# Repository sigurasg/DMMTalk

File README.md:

# DMMTalk

A battery-powered appendix to UNI-T 61E that speaks the settings and readings.

# TODO

* Add photodiode and amplifier for serial reception.
* Add button.
* Add volume control.
  * These two might take the form of a quadrature encoder with a button.
* Add headphone jack.
* Find a suitable SPI FLASH ROM.
  * Maybe [AT45DB081E
](http://www.adestotech.com/wp-content/uploads/DS-45DB081E_028.pdf)
  * Create a library component for same.
* Wire MSP430G2553 up.
  * RST/TEST go to RTS/CTS through resistors to allow BSL.
  * Need to find out how FT230 behaves without power, hopefully its outputs are
    3-state.
  * Even if it's tri-state, it'll conduct through the ESD protection diode, so
    this requires a switch to isolate the powered-down serial chip from
    the reset pin, as well as the TEST pin, to make sure in-circuit programming
    through the two-wire protocol works. Maybe something like
    http://www.onsemi.com/pub_link/Collateral/NL7WB66-D.PDF.
  * UCA0 or UCB0 drives the SPI bus.
  * One pin controls the analog power switch.
* Find suitable rail-to-rail op-amps.
  * Need 1.8V operating voltage at the bottom.
  * Need reasonable output current drive capability.
  * Maybe a bridge-drive headphone or speaker amp is better?

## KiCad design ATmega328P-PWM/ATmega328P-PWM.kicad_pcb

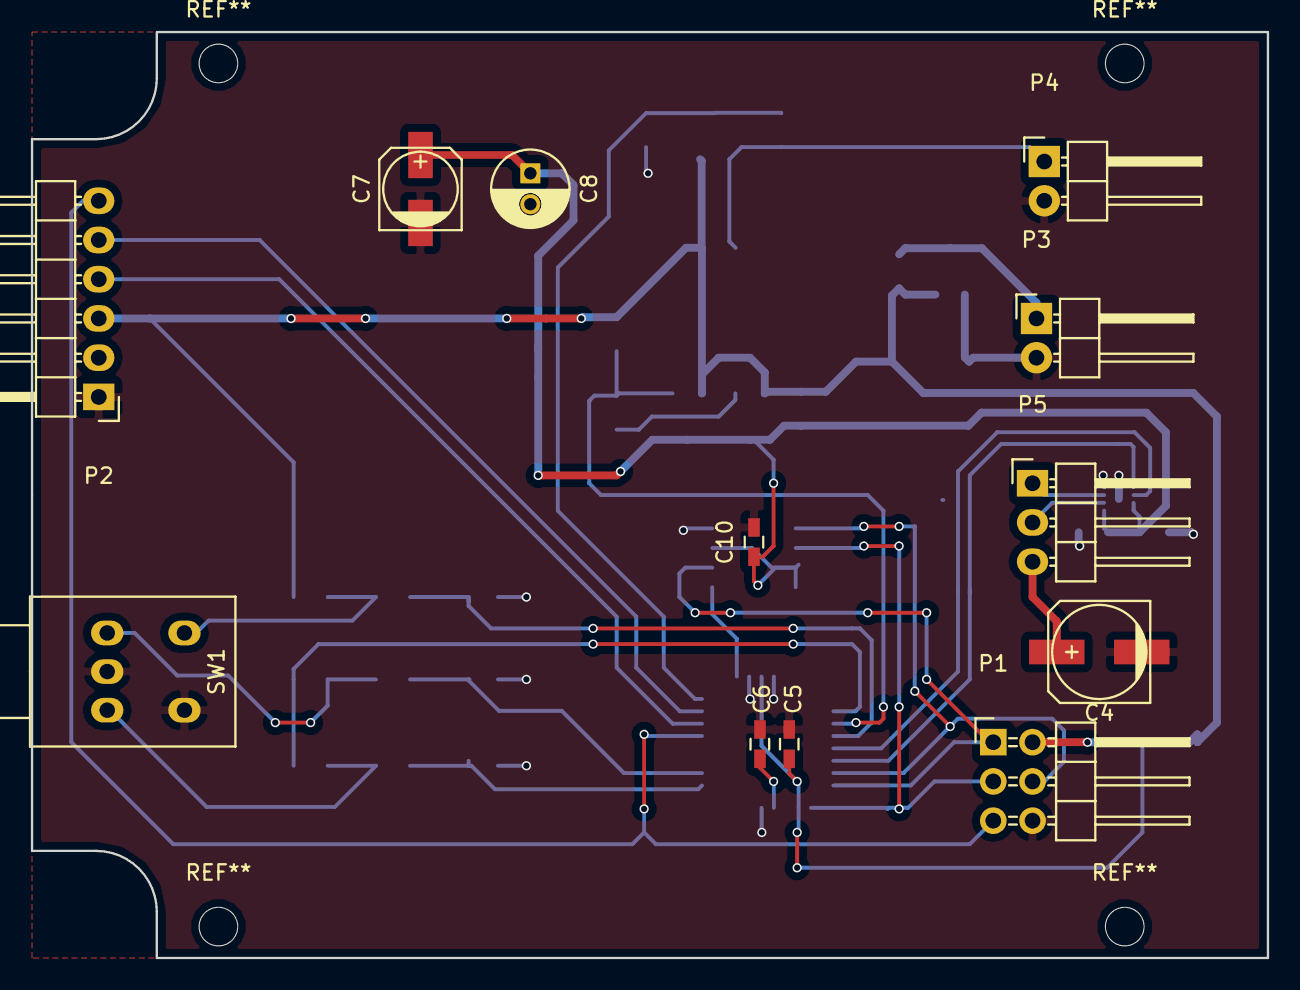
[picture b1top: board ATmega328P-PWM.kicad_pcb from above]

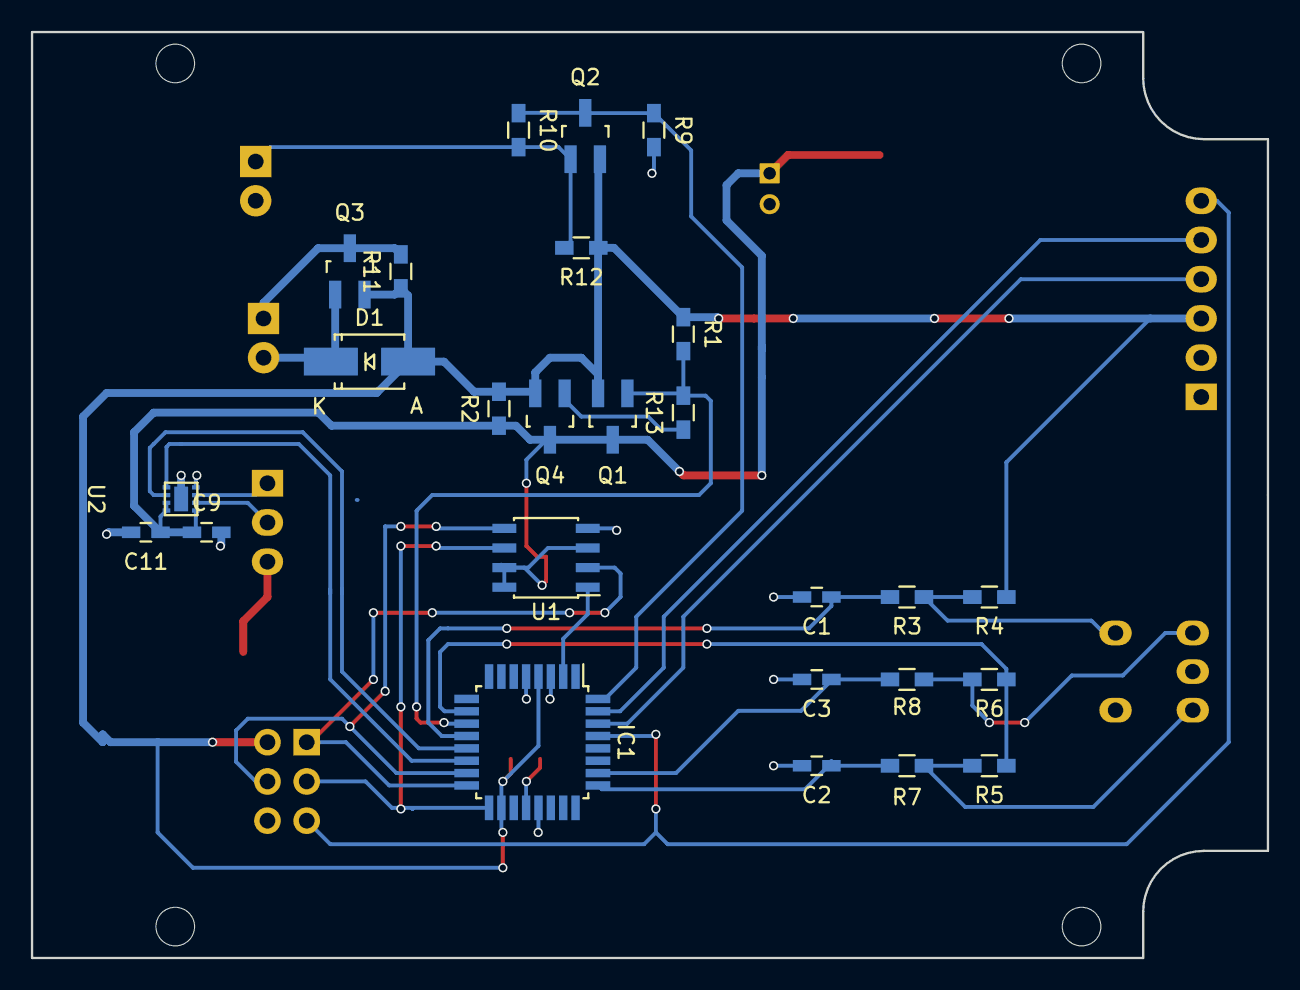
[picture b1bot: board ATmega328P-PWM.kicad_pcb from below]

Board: 2 copper layers, 80.0 x 59.9 mm, 38 parts (26 on the bottom side), 28 nets.

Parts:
C1, C2, C3: 0.01u; C_0603_HandSoldering
C4: 47u; c_elec_6.3x5.7
C5, C6, C9, C10, C11: 100n; C_0603_HandSoldering
C7: 47u; c_elec_5x5.3
C8: 47u; C_Radial_D5_L11_P2
D1: D; SMA_Handsoldering
IC1: ATMEGA328P-M; TQFP-32_7x7mm_Pitch0.8mm
P1: AVR_ISP; Pin_Header_Angled_2x03
P2: FTDI_HDR; Pin_Header_Angled_1x06
P3: BAT; Pin_Header_Angled_1x02
P4: PHOTODIODE; Pin_Header_Angled_1x02
P5: SPK; Pin_Header_Angled_1x03
Q1, Q3: IRLML6401; SOT-23_Handsoldering
Q2, Q4: MMBT3906; SOT-23_Handsoldering
R1: 330K; R_0603_HandSoldering
R2, R10, R11: 0; R_0603_HandSoldering
R3, R4, R5, R6, R7, R8: 10K; R_0603_HandSoldering
R9: 100K; R_0603_HandSoldering
R12: 100k; R_0603_HandSoldering
R13: 1k; R_0603_HandSoldering
SW1: PEC092320FS0015
U1: AT25DF041B; SOIC-8_3.9x4.9mm_Pitch1.27mm
U2: DRV8837; S-PWSON-N8

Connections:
//FLASH_CS: IC1.2, U1.1
//RESET: IC1.29, P1.5, P2.6
//VAUX_ON: IC1.11, Q1.1, R1.2, R13.2
/ENC_A: C2.1, IC1.25, R7.1
/ENC_B: C3.1, IC1.26, R8.1
/ENC_BUT: C1.1, IC1.12, R3.2
/ENC_HI: IC1.10, R5.1, R6.1
/MISO: IC1.16, P1.1, U1.2
/MOSI: IC1.15, P1.4, U1.5
/PHOTOD: IC1.32, Q2.3, R9.1, R10.1
/PWM_1: IC1.13, U2.6
/PWM_2: IC1.14, U2.5
/RX: IC1.30, P2.4
/SCK: IC1.17, P1.3, U1.6
/SPK1: P5.2, U2.2
/SPK2: P5.1, U2.3
/TX: IC1.31, P2.5
/VAUX: C7.1, C8.1, C9.1, C10.1, C11.1, Q1.3, Q4.3, R2.1, U1.3, U1.7, U1.8, U2.1, U2.7, U2.8
GND: C1.2, C2.2, C3.2, C4.2, C5.2, C6.2, C7.2, C8.2, C9.2, C10.2, C11.2, D1.1, IC1.3, IC1.5, IC1.21, P1.6, P2.1, P3.2, P4.2, Q3.1, R9.2, SW1.2, SW1.4, U1.4, U2.4
unnamed: C4.1, P5.3
unnamed: C6.1, IC1.20
unnamed: P3.1, Q3.3, R11.2
unnamed: P4.1, Q2.1, R10.2, R12.2
unnamed: Q4.1, R13.1
unnamed: R3.1, R4.2, SW1.1
unnamed: R5.2, R7.2, SW1.5
unnamed: R6.2, R8.2, SW1.3
VCC: C5.1, D1.2, IC1.4, IC1.6, IC1.18, P1.2, P2.3, Q1.2, Q2.2, Q3.2, Q4.2, R1.1, R2.2, R4.1, R11.1, R12.1

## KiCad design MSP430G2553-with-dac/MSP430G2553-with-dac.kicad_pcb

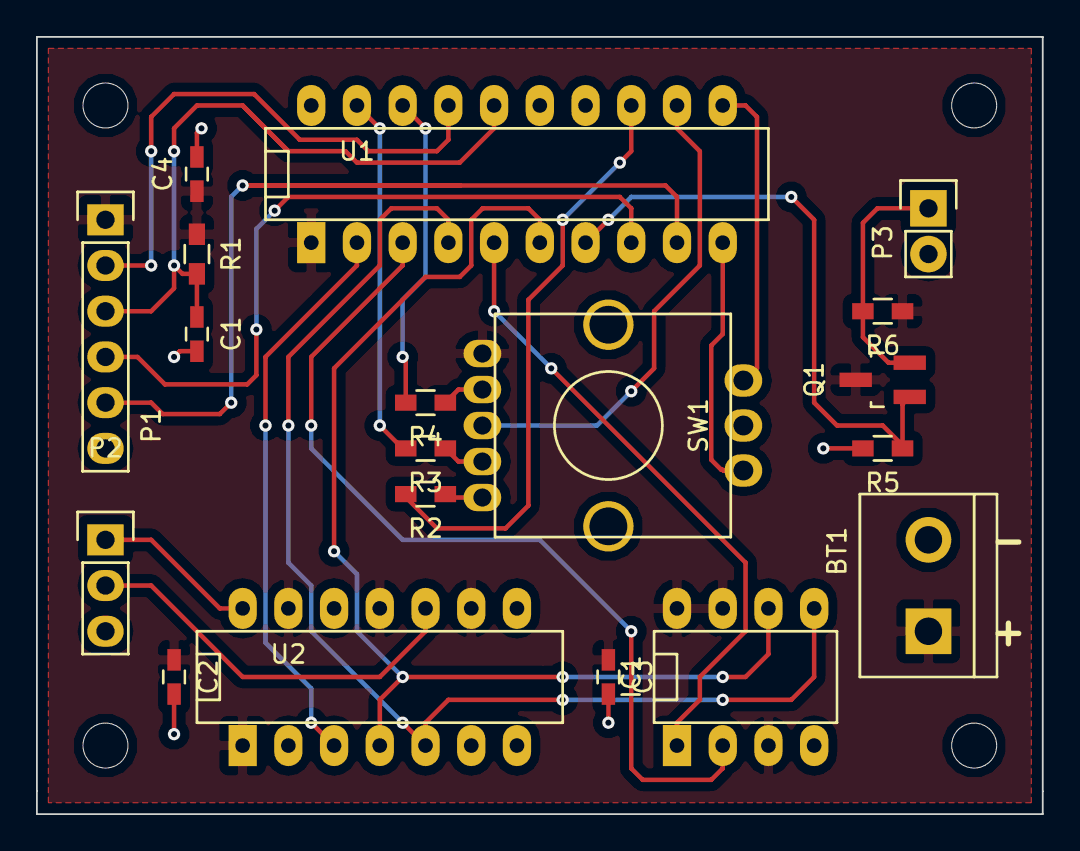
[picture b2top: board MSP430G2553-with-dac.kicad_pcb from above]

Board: 2 copper layers, 55.9 x 43.2 mm, 19 parts (0 on the bottom side), 24 nets.

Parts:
BT1: Battery; bornier2
C1: 1n; C_0603_HandSoldering
C2, C3, C4: 100n; C_0603_HandSoldering
IC1: MX25L4006E; DIP-8__300_ELL
P1: DEBUG; Pin_Header_Straight_1x06
P2: OUT; Pin_Header_Straight_1x03
P3: PHOTODIODE; Pin_Header_Straight_1x02
Q1: 2N3906; SOT-23_Handsoldering
R1: 47K; R_0603_HandSoldering
R2, R3, R4: 220; R_0603_HandSoldering
R5, R6: 100K; R_0603_HandSoldering
SW1: PEL12T
U1: MSP430G2553IN20; DIP-20__300_ELL
U2: MCP4922-E/P; DIP-14__300_ELL

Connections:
/A_OUT: P2.1, U2.14
/BLED: R4.2, U1.18
/BUTTON: SW1.3, U1.12
/B_OUT: P2.2, U2.10
/DACCS#: U1.2, U2.3
/FLASHCS#: IC1.1, U1.5
/GLED: R3.2, U1.19
/PH_IN: Q1.1, R5.1, U1.7
/Q_A: SW1.8, U1.10
/Q_B: SW1.6, U1.11
/RLED: R2.2, U1.13
/RST#: C1.1, P1.3, R1.2, U1.16
/RXD: P1.4, U1.8
/SCK: IC1.6, U1.6, U2.4
/SDI: IC1.5, U1.4, U2.5
/SDO: IC1.2, U1.3
/TEST: P1.2, U1.17
/TXD: P1.5, U1.9
GND: BT1.2, C1.2, C2.2, C3.2, C4.2, IC1.4, P1.6, P2.3, P3.2, R5.2, SW1.7, U1.20, U2.8, U2.12
unnamed: P3.1, Q1.2, R6.2
unnamed: R2.1, SW1.1
unnamed: R3.1, SW1.2
unnamed: R4.1, SW1.4
VCC: BT1.1, C2.1, C3.1, C4.1, IC1.3, IC1.7, IC1.8, P1.1, Q1.3, R1.1, R6.1, SW1.5, U1.1, U2.1, U2.9, U2.11, U2.13

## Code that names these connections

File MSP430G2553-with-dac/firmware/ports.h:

#ifndef PORTS_H_
#define PORTS_H_

#define nullptr 0


// Port 2
// @{

// Hardware pins.
#define RX BIT0
#define TX BIT1

#define Q_A BIT2
#define Q_B BIT3
#define BUTTON BIT4

// The LEDs are inverted, pull down to turn LEDs on.
#define RLED BIT5
#define GLED BIT6
#define BLED BIT7
#define LEDMASK (RLED | GLED | BLED)

// @}

#endif PORTS_H_

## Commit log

2015-04-20 Start DMMTalk.
2015-04-20 Add 47pF caps on USB, add a TODO list.
2015-04-25 Migrate to ToT KiCAD.
2015-04-26 Update README.md, remove .bak file.
2015-04-26 Work on a few things.
2015-05-07 Make a start on MSP430G2553 with DAC et al.
2015-05-10 430/DAC board laid out. Probably badly
2015-05-10 Ready for manufacture.
2015-06-03 Cosmetic changes + start firmware.
2015-06-05 Make a start on a generic time service.
2015-06-05 WIP: Wire LED PWM to timer.
2015-06-06 Fix many things; interrupt handling, timer chaining, button interrupt edge, quadrature edge setup, etc.
2015-06-06 Signed time to survive rollover. Fix quadrature mask setup. Eliminate flicker on LED setup.
2015-06-06 Moar time rollover fixing.
2015-06-06 Fix de-bouncing and now really fix rollover - really.
2015-06-06 Rename some functions, move timer code to a separate file.
2015-06-06 Get rid of 1us glitch on each LED PWM period. Cosmetic cleanup.
2015-06-07 Hello world bitbanging serial. WIP.
2015-06-24 Format to Google style. Use timer to output serial. Works in debug, as bit timing is largely code optimization-independent.
2015-10-17 Add volatile to critical variable. Cosmetics.
2015-10-24 Drop the HelloWorld code.
2015-10-24 Move the LED PWM code to a separate set of files.
2015-10-24 Move button code to a pair of files.
2015-11-22 Shuffle some code around
2015-11-22 Design files for an AtMega version of DMMTalk.
2015-11-22 Add serial files.
2015-11-28 Change encoder to PEC09.
2015-12-13 Add bypassing and associate footprints.
2016-10-02 Layout, but poorly.
